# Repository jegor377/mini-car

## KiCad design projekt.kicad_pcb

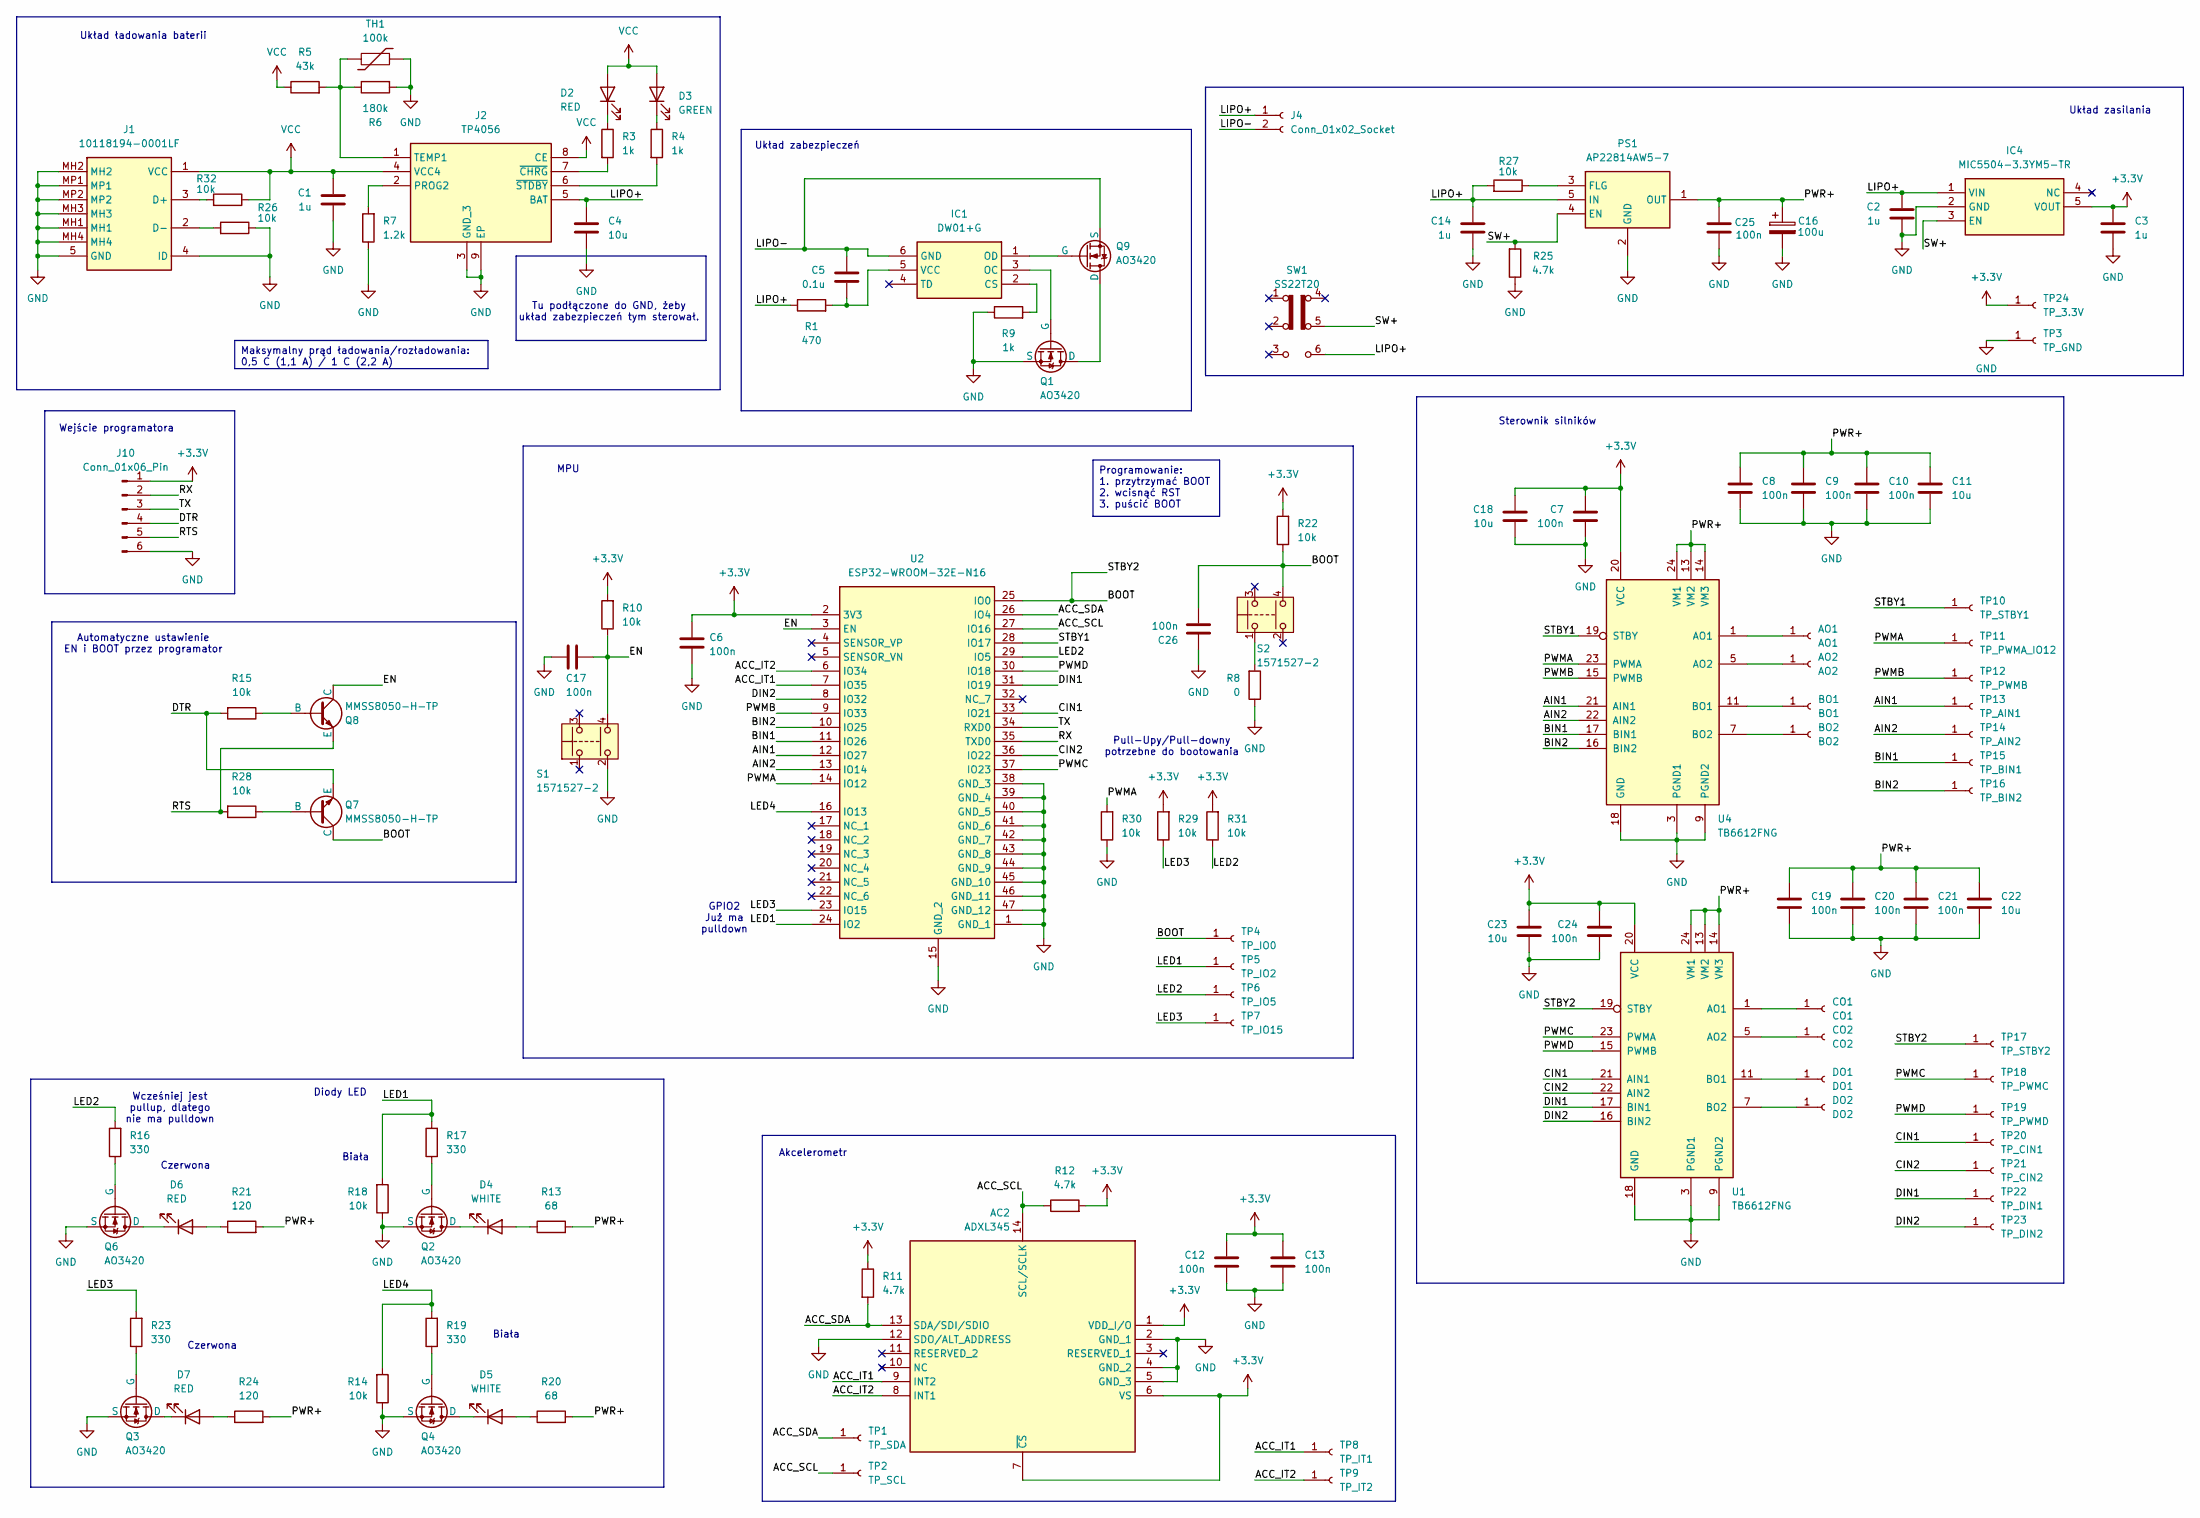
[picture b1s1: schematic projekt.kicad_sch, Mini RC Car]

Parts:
AC2: ADXL345; CC-14-1; Manufacturer_Part_Number ADXL345; Mouser Part Number N/A
AO1: AO1; TestPoint_Pad_2.0x2.0mm
AO2: AO2; TestPoint_Pad_2.0x2.0mm
BO1: BO1; TestPoint_Pad_2.0x2.0mm
BO2: BO2; TestPoint_Pad_2.0x2.0mm
C1, C2, C3, C14: 1u; C_0603_1608Metric_Pad1.08x0.95mm_HandSolder
C4, C11, C18, C22, C23: 10u; C_0603_1608Metric_Pad1.08x0.95mm_HandSolder
C5: 0.1u; C_0603_1608Metric_Pad1.08x0.95mm_HandSolder
C6, C7, C8, C9, C10, C12, C13, C17, C19, C20, C21, C24, C25, C26: 100n; C_0603_1608Metric_Pad1.08x0.95mm_HandSolder
C16: 100u; CP_Elec_5x5.3
CO1: CO1; TestPoint_Pad_2.0x2.0mm
CO2: CO2; TestPoint_Pad_2.0x2.0mm
D2, D6, D7: RED; LED_0805_2012Metric_Pad1.15x1.40mm_HandSolder
D3: GREEN; LED_0805_2012Metric_Pad1.15x1.40mm_HandSolder
D4, D5: WHITE; LED_0805_2012Metric_Pad1.15x1.40mm_HandSolder
DO1: DO1; TestPoint_Pad_2.0x2.0mm
DO2: DO2; TestPoint_Pad_2.0x2.0mm
IC1: DW01+G; SOT95P280X145-6N; Manufacturer_Part_Number DW01+G
IC4: MIC5504-3.3YM5-TR; SOT95P280X145-5N; Manufacturer_Part_Number MIC5504-3.3YM5-TR; Mouser Part Number 998-MIC5504-3.3YM5TR
J1: 10118194-0001LF; 101181940001LF; Manufacturer_Part_Number 10118194-0001LF
J2: TP4056; SOIC127P600X175-9N; Manufacturer_Part_Number TP4056
J4: Conn_01x02_Socket; JST_XH_B2B-XH-A_1x02_P2.50mm_Vertical
J10: Conn_01x06_Pin; PinHeader_1x06_P2.54mm_Vertical
PS1: AP22814AW5-7; SOT95P285X130-5N; Manufacturer_Part_Number AP22814AW5-7; Mouser Part Number 621-AP22814AW5-7
Q1, Q2, Q3, Q4, Q6, Q9: AO3420; SOT95P280X125-3N; Manufacturer_Part_Number AO3420
Q7, Q8: MMSS8050-H-TP; SOT95P237X125-3N; Manufacturer_Part_Number MMSS8050-H-TP
R1: 470; R_0603_1608Metric_Pad0.98x0.95mm_HandSolder
R3, R4, R9: 1k; R_0603_1608Metric_Pad0.98x0.95mm_HandSolder
R5: 43k; R_0603_1608Metric_Pad0.98x0.95mm_HandSolder
R6: 180k; R_0603_1608Metric_Pad0.98x0.95mm_HandSolder
R7: 1.2k; R_0603_1608Metric_Pad0.98x0.95mm_HandSolder
R8: 0; R_0603_1608Metric_Pad0.98x0.95mm_HandSolder
R10, R14, R15, R18, R22, R26, R27, R28, R29, R30, R31, R32: 10k; R_0603_1608Metric_Pad0.98x0.95mm_HandSolder
R11, R12, R25: 4.7k; R_0603_1608Metric_Pad0.98x0.95mm_HandSolder
R13, R20: 68; R_0603_1608Metric_Pad0.98x0.95mm_HandSolder
R16, R17, R19, R23: 330; R_0603_1608Metric_Pad0.98x0.95mm_HandSolder
R21, R24: 120; R_0603_1608Metric_Pad0.98x0.95mm_HandSolder
S1, S2: 1571527-2; 15715272; Manufacturer_Part_Number 1571527-2
SW1: SS22T20
TH1: 100k; Termistor_SMD
TP1: TP_SDA; TestPoint_Pad_2.0x2.0mm
TP2: TP_SCL; TestPoint_Pad_2.0x2.0mm
TP3: TP_GND; TestPoint_Pad_2.0x2.0mm
TP4: TP_IO0; TestPoint_Pad_2.0x2.0mm
TP5: TP_IO2; TestPoint_Pad_2.0x2.0mm
TP6: TP_IO5; TestPoint_Pad_2.0x2.0mm
TP7: TP_IO15; TestPoint_Pad_2.0x2.0mm
TP8: TP_IT1; TestPoint_Pad_2.0x2.0mm
TP9: TP_IT2; TestPoint_Pad_2.0x2.0mm
TP10: TP_STBY1; TestPoint_Pad_2.0x2.0mm
TP11: TP_PWMA_IO12; TestPoint_Pad_2.0x2.0mm
TP12: TP_PWMB; TestPoint_Pad_2.0x2.0mm
TP13: TP_AIN1; TestPoint_Pad_2.0x2.0mm
TP14: TP_AIN2; TestPoint_Pad_2.0x2.0mm
TP15: TP_BIN1; TestPoint_Pad_2.0x2.0mm
TP16: TP_BIN2; TestPoint_Pad_2.0x2.0mm
TP17: TP_STBY2; TestPoint_Pad_2.0x2.0mm
TP18: TP_PWMC; TestPoint_Pad_2.0x2.0mm
TP19: TP_PWMD; TestPoint_Pad_2.0x2.0mm
TP20: TP_CIN1; TestPoint_Pad_2.0x2.0mm
TP21: TP_CIN2; TestPoint_Pad_2.0x2.0mm
TP22: TP_DIN1; TestPoint_Pad_2.0x2.0mm
TP23: TP_DIN2; TestPoint_Pad_2.0x2.0mm
TP24: TP_3.3V; TestPoint_Pad_2.0x2.0mm
U1, U4: TB6612FNG; SSOP-24_5.3x8.2mm_P0.65mm
U2: ESP32-WROOM-32E-N16; ESP32WROOM32EN16; Manufacturer_Part_Number ESP32-WROOM-32E-N16

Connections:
+3.3V: AC2.1 (VDD_I/O), AC2.6 (VS), AC2.7 (~CS), C3.1, C6.1, C7.1, C12.1, C13.1, C18.1, C23.1, C24.1, IC4.5 (VOUT), J10.1, R10.2, R11.1, R12.2, R22.2, R29.2, R31.2, TP24.1, U1.20 (VCC), U2.2 (3V3), U4.20 (VCC)
/ACC_IT1: AC2.9 (INT2), TP8.1, U2.7 (IO35)
/ACC_IT2: AC2.8 (INT1), TP9.1, U2.6 (IO34)
/ACC_SCL: AC2.14 (SCL/SCLK), R12.1, TP2.1, U2.27 (IO16)
/ACC_SDA: AC2.13 (SDA/SDI/SDIO), R11.2, TP1.1, U2.26 (IO4)
/AIN1: TP13.1, U2.12 (IO27), U4.21 (AIN1)
/AIN2: TP14.1, U2.13 (IO14), U4.22 (AIN2)
/BIN1: TP15.1, U2.11 (IO26), U4.17 (BIN1)
/BIN2: TP16.1, U2.10 (IO25), U4.16 (BIN2)
/BOOT: C26.2, Q7.3 (C), R22.1, S2.4, TP4.1, TP17.1, U1.19 (STBY), U2.25 (IO0)
/CIN1: TP20.1, U1.21 (AIN1), U2.33 (IO21)
/CIN2: TP21.1, U1.22 (AIN2), U2.36 (IO22)
/DIN1: TP22.1, U1.17 (BIN1), U2.31 (IO19)
/DIN2: TP23.1, U1.16 (BIN2), U2.8 (IO32)
/DTR: J10.4, Q7.2 (E), R15.2
/EN: C17.1, Q8.3 (C), R10.1, S1.4, U2.3 (EN)
/LED1: R17.2, R18.2, TP5.1, U2.24 (IO2)
/LED2: R16.2, R31.1, TP6.1, U2.29 (IO5)
/LED3: R23.2, R29.1, TP7.1, U2.23 (IO15)
/LED4: R14.2, R19.2, U2.16 (IO13)
/LIPO+: C2.1, C4.1, C14.2, IC4.1 (VIN), J2.5 (BAT), J4.1, PS1.5 (IN), R1.1, R27.2, SW1.6 (C)
/LIPO-: C5.1, IC1.6 (GND), J4.2, Q9.2 (S)
/PWMA: R30.2, TP11.1, U2.14 (IO12), U4.23 (PWMA)
/PWMB: TP12.1, U2.9 (IO33), U4.15 (PWMB)
/PWMC: TP18.1, U1.23 (PWMA), U2.37 (IO23)
/PWMD: TP19.1, U1.15 (PWMB), U2.30 (IO18)
/PWR+: C8.1, C9.1, C10.1, C11.1, C16.1, C19.1, C20.1, C21.1, C22.1, C25.1, PS1.1 (OUT), R13.2, R20.2, R21.2, R24.2, U1.13 (VM2), U1.14 (VM3), U1.24 (VM1), U4.13 (VM2), U4.14 (VM3), U4.24 (VM1)
/RTS: J10.5, Q8.2 (E), R28.2
/RX: J10.2, U2.35 (TXD0)
/STBY1: TP10.1, U2.28 (IO17), U4.19 (STBY)
/SW+: IC4.3 (EN), PS1.4 (EN), R25.2, SW1.5 (B)
/TX: J10.3, U2.34 (RXD0)
GND: AC2.2 (GND_1), AC2.4 (GND_2), AC2.5 (GND_3), AC2.12 (SDO/ALT_ADDRESS), C1.1, C2.2, C3.2, C4.2, C6.2, C7.2, C8.2, C9.2, C10.2, C11.2, C12.2, C13.2, C14.1, C16.2, C17.2, C18.2, C19.2, C20.2, C21.2, C22.2, C23.2, C24.2, C25.2, C26.1, IC4.2 (GND), J1.4 (ID), J1.5 (GND), J1.MH1, J1.MH2, J1.MH3, J1.MH4, J1.MP1, J1.MP2, J2.3 (GND_3), J2.9 (EP), J10.6, PS1.2 (GND), Q1.2 (S), Q2.2 (S), Q3.2 (S), Q4.2 (S), Q6.2 (S), R6.2, R7.1, R8.1, R9.1, R14.1, R18.1, R25.1, R26.1, R30.1, S1.2, TH1.1, TP3.1, U1.3 (PGND1), U1.4 (PGND1), U1.9 (PGND2), U1.10 (PGND2), U1.18 (GND), U2.1 (GND_1), U2.15 (GND_2), U2.38 (GND_3), U2.39 (GND_4), U2.40 (GND_5), U2.41 (GND_6), U2.42 (GND_7), U2.43 (GND_8), U2.44 (GND_9), U2.45 (GND_10), U2.46 (GND_11), U2.47 (GND_12), U4.3 (PGND1), U4.4 (PGND1), U4.9 (PGND2), U4.10 (PGND2), U4.18 (GND)
unnamed: AO1.1, U4.1 (AO1), U4.2 (AO1)
unnamed: AO2.1, U4.5 (AO2), U4.6 (AO2)
unnamed: BO1.1, U4.11 (BO1), U4.12 (BO1)
unnamed: BO2.1, U4.7 (BO2), U4.8 (BO2)
unnamed: CO1.1, U1.1 (AO1), U1.2 (AO1)
unnamed: CO2.1, U1.5 (AO2), U1.6 (AO2)
unnamed: D2.1 (K), R3.1
unnamed: D3.1 (K), R4.1
unnamed: D4.2 (A), R13.1
unnamed: D4.1 (K), Q2.3 (D)
unnamed: D5.2 (A), R20.1
unnamed: D5.1 (K), Q4.3 (D)
unnamed: D6.2 (A), R21.1
unnamed: D6.1 (K), Q6.3 (D)
unnamed: D7.2 (A), R24.1
unnamed: D7.1 (K), Q3.3 (D)
unnamed: DO1.1, U1.11 (BO1), U1.12 (BO1)
unnamed: DO2.1, U1.7 (BO2), U1.8 (BO2)
unnamed: IC1.2 (CS), R9.2
unnamed: IC1.3 (OC), Q1.1 (G)
unnamed: IC1.1 (OD), Q9.1 (G)
unnamed: C5.2, IC1.5 (VCC), R1.2
unnamed: J1.3 (D+), R32.2
unnamed: J1.2 (D-), R26.2
unnamed: J2.2 (PROG2), R7.2
unnamed: J2.1 (TEMP1), R5.2, R6.1, TH1.2
unnamed: J2.7 (~CHRG), R3.2
unnamed: J2.6 (~STDBY), R4.2
unnamed: PS1.3 (FLG), R27.1
unnamed: Q1.3 (D), Q9.3 (D)
unnamed: Q2.1 (G), R17.1
unnamed: Q3.1 (G), R23.1
unnamed: Q4.1 (G), R19.1
unnamed: Q6.1 (G), R16.1
unnamed: Q7.1 (B), R28.1
unnamed: Q8.1 (B), R15.1
unnamed: R8.2, S2.1
VCC: C1.2, D2.2 (A), D3.2 (A), J1.1 (VCC), J2.4 (VCC4), J2.8 (CE), R5.1, R32.1

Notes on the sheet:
Programowanie: 1. przytrzymać BOOT 2. wcisnąć RST 3. puścić BOOT
Maksymalny prąd ładowania/rozładowania: 0,5 C (1,1 A) / 1 C (2,2 A)
Pull-Upy/Pull-downy potrzebne do bootowania
Tu podłączone do GND, żeby układ zabezpieczeń tym sterował.
Automatyczne ustawienie EN i BOOT przez programator
Wejście programatora
Czerwona
Sterownik silników
Diody LED
Wcześniej jest pullup, dlatego nie ma pulldown
Układ ładowania baterii
Biała
Akcelerometr
Układ zasilania
MPU
Układ zabezpieczeń
GPIO2 Już ma pulldown

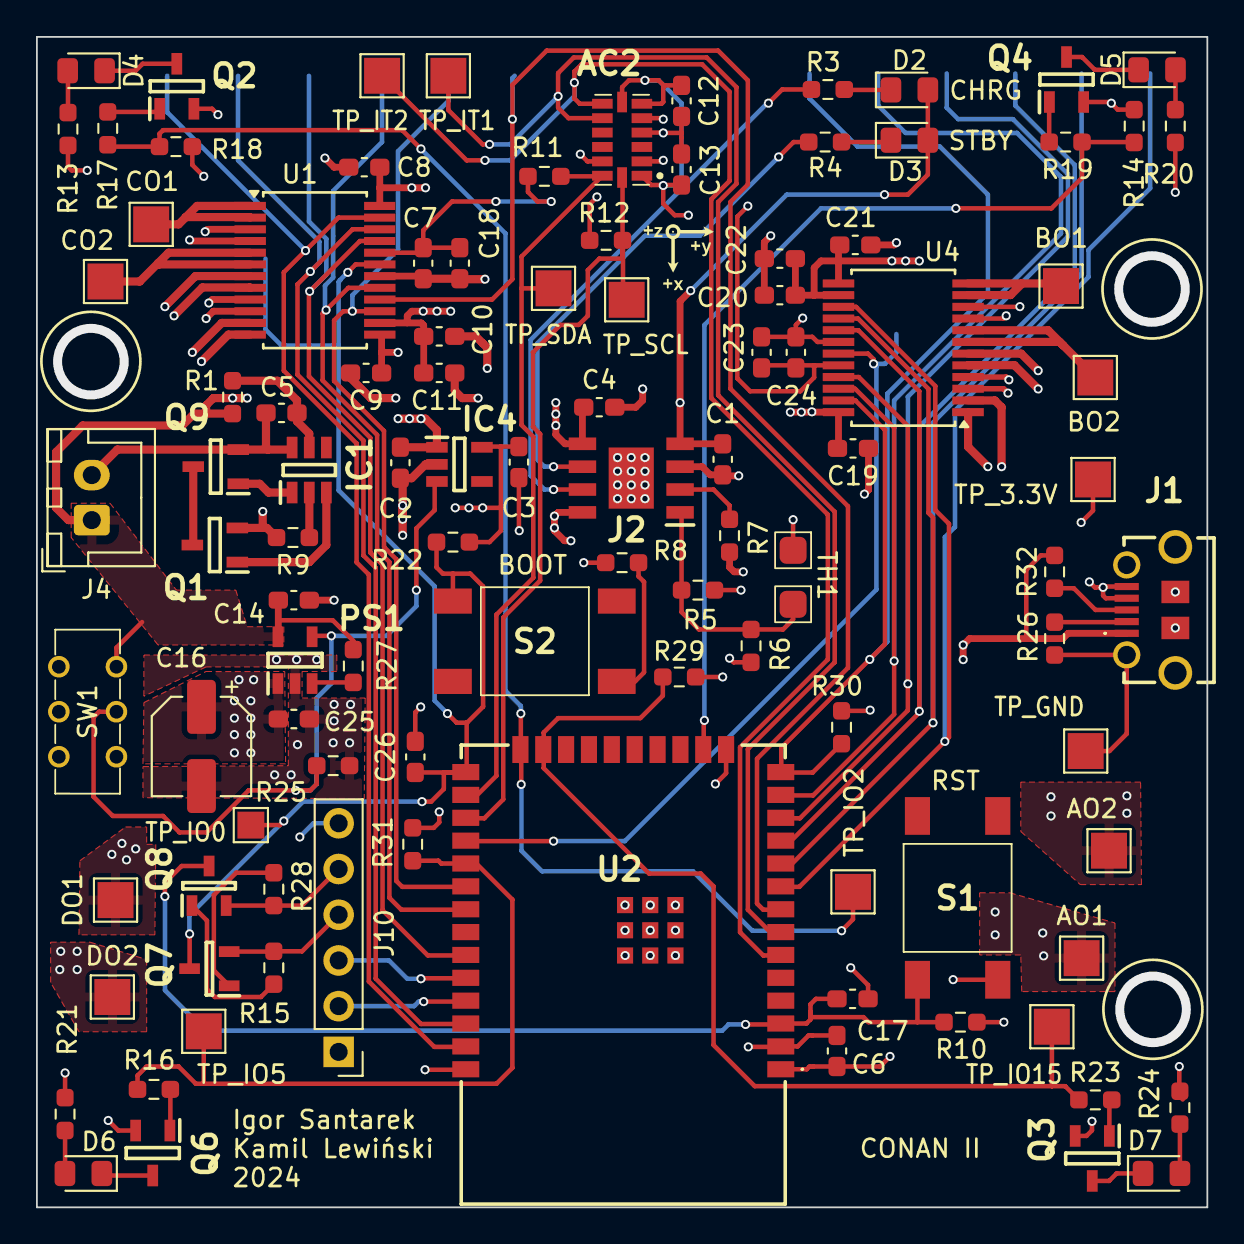
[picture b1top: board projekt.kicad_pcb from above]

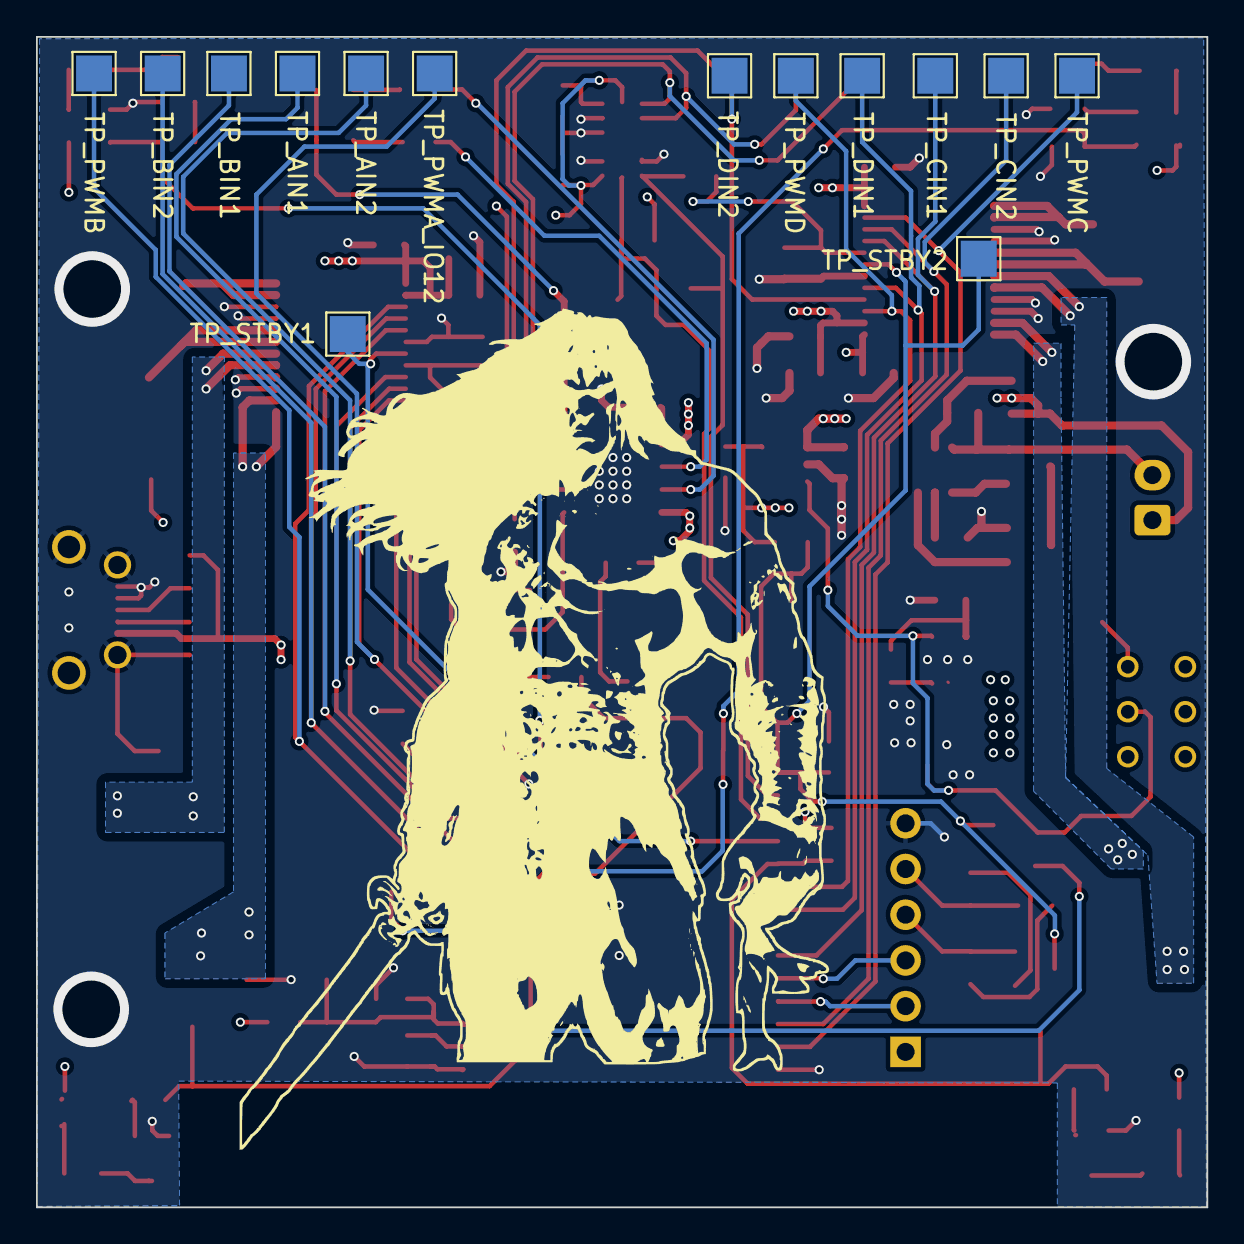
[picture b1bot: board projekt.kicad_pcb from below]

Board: 4 copper layers, 65.0 x 65.0 mm, 117 parts (14 on the bottom side), 71 nets.

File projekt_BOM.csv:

"Reference","Value","Datasheet","Footprint","Qty","DNP"
"AC2","ADXL345","http://www.analog.com/media/en/technical-documentation/data-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","CC-14-1","1",""
"C1,C2,C3,C14","1u","~","Capacitor_SMD:C_0603_1608Metric_Pad1.08x0.95mm_HandSolder","4",""
"C4,C11,C18,C22,C23","10u","~","Capacitor_SMD:C_0603_1608Metric_Pad1.08x0.95mm_HandSolder","5",""
"C5","0.1u","~","Capacitor_SMD:C_0603_1608Metric_Pad1.08x0.95mm_HandSolder","1",""
"C6,C7,C8,C9,C10,C12,C13,C17,C19,C20,C21,C24,C25,C26","100n","~","Capacitor_SMD:C_0603_1608Metric_Pad1.08x0.95mm_HandSolder","14",""
"C16","100u","~","Capacitor_SMD:CP_Elec_5x5.3","1",""
"D2","GREEN","~","LED_SMD:LED_0805_2012Metric_Pad1.15x1.40mm_HandSolder","1",""
"D3,D6,D7","RED","~","LED_SMD:LED_0805_2012Metric_Pad1.15x1.40mm_HandSolder","3",""
"D4,D5","WHITE","~","LED_SMD:LED_0805_2012Metric_Pad1.15x1.40mm_HandSolder","2",""
"IC1","DW01+G","https://datasheet.lcsc.com/szlcsc/Fortune-Semicon-DW01-G_C14213.pdf","SOT95P280X145-6N","1",""
"IC4","MIC5504-3.3YM5-TR","https://componentsearchengine.com/Datasheets/2/MIC5504-3.3YM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","SOT95P280X145-5N","1",""
"J1","10118194-0001LF","https://www.amphenol-cs.com/micro-usb-101181940001lf.html","101181940001LF","1",""
"J2","TP4056","https://dlnmh9ip6v2uc.cloudfront.net/datasheets/Prototyping/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","SOIC127P600X175-9N","1",""
"J4","Conn_01x02_Socket","~","Connector_JST:JST_XH_B2B-XH-A_1x02_P2.50mm_Vertical","1",""
"J10","Conn_01x06_Pin","~","Connector_PinHeader_2.54mm:PinHeader_1x06_P2.54mm_Vertical","1",""
"PS1","AP22814AW5-7","https://componentsearchengine.com/Datasheets/2/AP22814AW5-7.pdf","SOT95P285X130-5N","1",""
"Q1,Q2,Q3,Q4,Q6,Q9","AO3420","https://ngspice.sourceforge.io/docs/ngspice-html-manual/manu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","SOT95P280X125-3N","6",""
"Q7,Q8","MMSS8050-H-TP","https://ngspice.sourceforge.io/docs/ngspice-html-manual/manu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","SOT95P237X125-3N","2",""
"R1","470","~","Resistor_SMD:R_0603_1608Metric_Pad0.98x0.95mm_HandSolder","1",""
"R3,R4,R9","1k","~","Resistor_SMD:R_0603_1608Metric_Pad0.98x0.95mm_HandSolder","3",""
"R5","43k","~","Resistor_SMD:R_0603_1608Metric_Pad0.98x0.95mm_HandSolder","1",""
"R6","180k","~","Resistor_SMD:R_0603_1608Metric_Pad0.98x0.95mm_HandSolder","1",""
"R7","1.2k","~","Resistor_SMD:R_0603_1608Metric_Pad0.98x0.95mm_HandSolder","1",""
"R8","0","~","Resistor_SMD:R_0603_1608Metric_Pad0.98x0.95mm_HandSolder","1",""
"R10,R14,R15,R18,R22,R26,R27,R28,R29,R30,R31,R32","10k","~","Resistor_SMD:R_0603_1608Metric_Pad0.98x0.95mm_HandSolder","12",""
"R11,R12,R25","4.7k","~","Resistor_SMD:R_0603_1608Metric_Pad0.98x0.95mm_HandSolder","3",""
"R13,R20","120","~","Resistor_SMD:R_0603_1608Metric_Pad0.98x0.95mm_HandSolder","2",""
"R16,R17,R19,R23","330","~","Resistor_SMD:R_0603_1608Metric_Pad0.98x0.95mm_HandSolder","4",""
"R21,R24","320","~","Resistor_SMD:R_0603_1608Metric_Pad0.98x0.95mm_HandSolder","2",""
"S1,S2","1571527-2","~","15715272","2",""
"SW1","SW_Slide_DPDT","~","Button_Switch_THT:SS22T20","1",""
"TH1","100k","~","Resistor_SMD:Termistor_SMD","1",""
"U1,U4","TB6612FNG","https://toshiba.semicon-storage.com/us/product/linear/motord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","Package_SO:SSOP-24_5.3x8.2mm_P0.65mm","2",""
"U2","ESP32-WROOM-32E-N16","https://www.espressif.com/sites/default/files/documentation/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","ESP32WROOM32EN16","1",""

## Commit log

2024-11-21 Start
2024-11-21 remove projekt-backups
2024-11-21 Dodanie gitignore
2024-11-22 Prawie skończony schemat.
2024-11-26 Prawie skończony schemat
2024-11-28 Potwarz dla ludzkości
2024-11-29 Gotowy schemat (albo prawie gotowy)
2024-11-29 Poprawienie footprintów i ustawień
2024-11-30 Dodanie drugiego DC IC
2024-12-01 Praca nad PCB
2024-12-01 wstępne ułożenie elementów
2024-12-01 Poprawienie schematu i PCB
2024-12-01 powoli nabiera koloru
2024-12-02 Milion błędów DRC do poprawienia
2024-12-06 prawie gotowe
2024-12-08 PRAWIE SKOŃCZONE
2024-12-08 ZERO DRC ERRORS OMG OMG OMG
2024-12-08 POWRÓT CONANA
2024-12-08 Poprawka conana
2024-12-08 Poprawka
2024-12-08 Finish
2024-12-08 Poprawione dziury montażowe
2024-12-08 teraz sprawdzić czy na pewno wszystko git
2024-12-08 final commit
2024-12-08 final commit2
2024-12-08 final commit3
2024-12-08 final commit4
2024-12-08 final commit5
2024-12-08 Podmiana tranzystorów
2024-12-08 Podmiana tranzystorów i symboli
2024-12-09 Podmiana przycisków
2024-12-09 Podmiana esp32 i footprinta switcha
2024-12-09 Podmiana ścieżek na plane w dolnych wyjściach silników
2024-12-09 Przed wygenerowaniem gerberów
2024-12-11 poprawienie włąściwości odprowadzania ciepła dla power switcha
2024-12-11 poprawienie przelotek
2024-12-11 Wysłane do produkcji
2024-12-11 Skończenie i wygenerowanie modelu 3D
2024-12-11 Dodanie grafiki
2024-12-11 Dodanie grafiki2
2024-12-11 Wygenerowanie BOMa interaktywnego
